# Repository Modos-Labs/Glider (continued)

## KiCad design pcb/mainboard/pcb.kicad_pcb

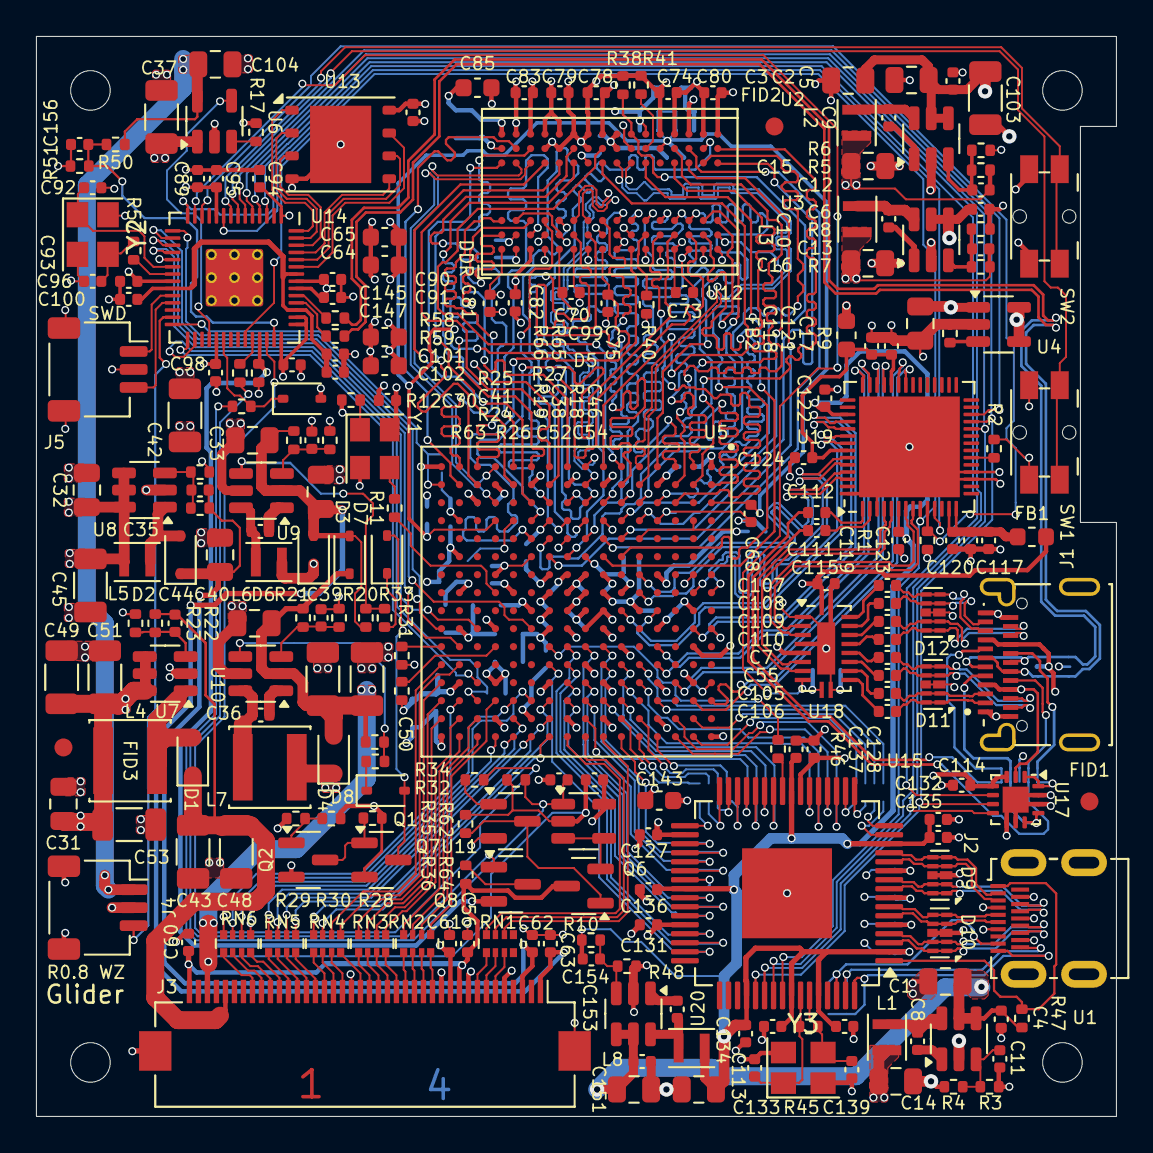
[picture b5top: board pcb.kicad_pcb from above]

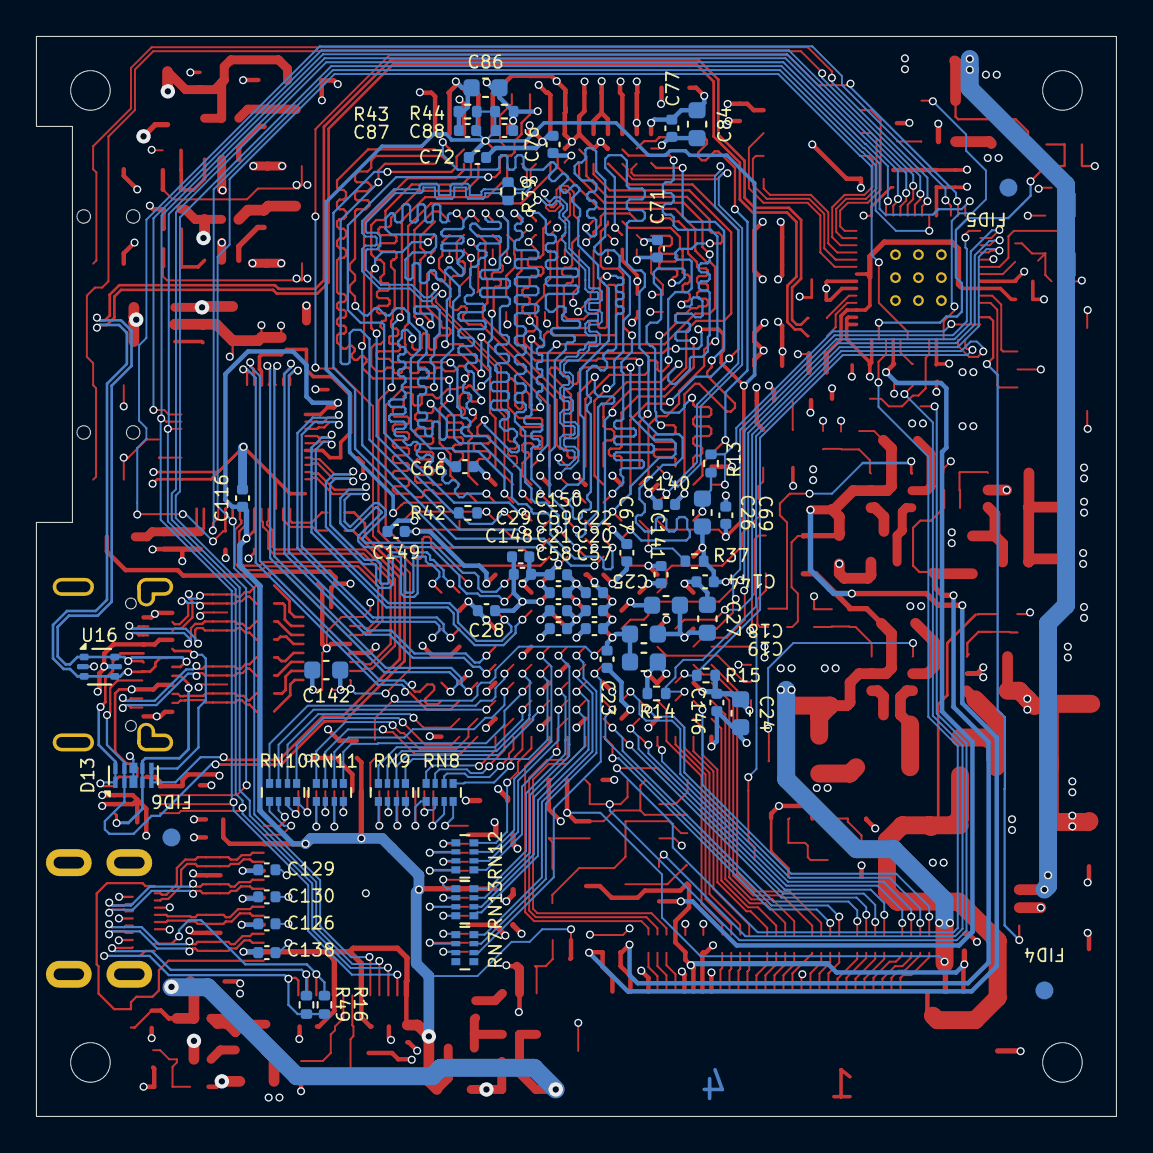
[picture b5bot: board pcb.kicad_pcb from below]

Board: 4 copper layers, 60.0 x 60.0 mm, 296 parts (61 on the bottom side), 307 nets.

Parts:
C1, C2, C3, C14, C15, C16, C17, C31, C32, C104, C151, C155: 10uF/10V; C_0805_2012Metric
C4, C5, C6, C7, C8, C9, C10, C35, C36, C54, C55, C87, C88, C90, C91, C94, C95, C96, C97, C98, C99, C100, C101, C105, C106, C107, C108, C109, C110, C111, C112, C114, C115, C119, C120, C121, C122, C123, C124, C127, C128, C129, C130, C131, C133, C134, C135, C136, C137, C138, C139, C152, C153, C156: 100nF; C_0402_1005Metric
C11, C12, C13, C154: 47pF; C_0402_1005Metric
C18, C19, C24, C25, C26, C27, C64, C65, C84, C85, C86, C142, C143, C145, C147: 47uF/6.3V; C_0603_1608Metric
C20, C22, C23, C28, C57, C59, C66, C144, C148: 4.7uF; C_0402_1005Metric
C21, C29, C58, C67, C140, C141, C146, C149, C150: 470nF; C_0402_1005Metric
C30, C52, C60, C61, C62, C63, C68, C69, C70, C71, C72, C73, C74, C75, C76, C77, C78, C79, C80, C81, C82, C83: 220nF; C_0402_1005Metric
C33, C34, C44, C46: 4.7uF/50V; C_0805_2012Metric
C37, C42, C45, C49, C51, C53, C103: 47uF/10V; C_1206_3216Metric
C38, C39, C40, C41, C92, C93, C113, C125: 18pF; C_0402_1005Metric
C43, C47, C48, C50: 10uF/50V; C_1206_3216Metric
C56, C89, C102, C116, C117, C118, C126, C132: 1uF; C_0402_1005Metric
D1, D2, D3, D4, D5, D6, D7, D8: B0530WS; D_SOD-323
D9, D10, D11, D12, D13: RCLAMP0524P; Diodes_UDFN-10_1.0x2.5mm_P0.5mm
FB1, FB2: 120R; L_0603_1608Metric
FID1, FID2, FID3, FID4, FID5, FID6: Fiducial; Fiducial_1mm_Mask2mm
H1, H2, H3, H4: MountingHole; MountingHole_2.2mm_M2_DIN965
J1: XUNPU TYPEC-324G-ACP24; XUNPU_TypeC-324G-ACP24
J2: XUNPU HDMI-101S; HDMI_Micro-D_Molex_46765-1x01_MOD
J3: FH12-40S-0.5SH; Hirose_FH12-40S-0.5SH_1x40-1MP_P0.50mm_Horizontal_Reversed
J4, J5: SM03B-SRSS-TB; JST_SH_SM03B-SRSS-TB_1x03-1MP_P1.00mm_Horizontal
L1, L2, L3, L5, L6, L8: FTC201610S4R7MBCA; L_Murata_DFE201610P
L4, L7: WPN4020H4R7MT; L_Changjiang_FNR4020S
Q1, Q7, Q8: AO3401A; SOT-23
Q2: S8050; SOT-23
Q6: AO3400A; SOT-23
R1, R2, R12, R13, R14, R21, R29, R38, R40, R42: 5.1K; R_0402_1005Metric
R3, R20, R26: 91K/1%; R_0402_1005Metric
R4, R5, R7, R8, R10, R64: 20K/1%; R_0402_1005Metric
R6: 16K/1%; R_0402_1005Metric
R9, R17, R19, R23, R25, R48, R65: 10K/1%; R_0402_1005Metric
R11, R46, R58, R59: 27R; R_0402_1005Metric
R15, R43, R44: 1K/1%; R_0402_1005Metric
R16, R47, R49: 10K; R_0402_1005Metric
R18, R22: 240K/1%; R_0402_1005Metric
R24: 360K/1%; R_0402_1005Metric
R27, R30: 27K/1%; R_0402_1005Metric
R28, R31, R32, R33, R34, R62: 120K/1%; R_0402_1005Metric
R35, R36: 0R; R_0402_1005Metric
R37, R39: 100R/1%; R_0402_1005Metric
R41: 240R/1%; R_0402_1005Metric
R45, R50, R51: 1M; R_0402_1005Metric
R57: 1K; R_0402_1005Metric
R63, R66: 51R; R_0402_1005Metric
RN1, RN2, RN3, RN4, RN5, RN6, RN7, RN8, RN9, RN10, RN11, RN12, RN13: 33R / 4D02WGF330JTCE; R_Array_Convex_4x0402
SW1, SW2: SW; Panasonic_EVQPUL_EVQPUC
U1, U2, U3, U20: SY8120; TSOT-23-6
U4, U6: MT9700; SOT-23-5
U5: XC6SLX16-FTG256; Xilinx_FTG256
U7, U8: MT3608(SOT23-6); SOT-23-6
U9, U10: LGS5148; TSOT-23-6
U11: LM321; SOT-23-5
U12: MT41K64M16TW; BGA-96_9.0x14.0mm_P0.8mm
U13: W25Q32JV; WSON-8-1EP_6x5mm_P1.27mm_EP3.4x4.3mm
U14: RP2040; RP2040-QFN-56
U15: ADV7611; LQFP-64-1EP_10x10mm_P0.5mm_EP5x5mm
U16: USBLC6-2P6; SOT-666
U17: FUSB302BMPX; WQFN-14-1EP_2.5x2.5mm_P0.5mm_EP1.45x1.45mm
U18: CBTL02043A; WQFN-20-1EP_2.5x4.5mm_P0.5mm_EP1x2.9mm
U19: PTN3460; QFN-56-1EP_7x7mm_P0.4mm_EP5.6x5.6mm
Y1: 33MHz; Oscillator_SMD_Abracon_ASE-4Pin_3.2x2.5mm
Y2: 12MHz; Crystal_SMD_3225-4Pin_3.2x2.5mm
Y3: 28.63636MHz; Crystal_SMD_3225-4Pin_3.2x2.5mm

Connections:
+1V2: C13.2, C16.2, C18.1, C19.1, C20.1, C21.1, C22.1, C23.1, C59.1, L3.2, R7.2, U5.G7 (VCCINT), U5.G9 (VCCINT), U5.H8 (VCCINT), U5.H10 (VCCINT), U5.J7 (VCCINT), U5.J9 (VCCINT), U5.K8 (VCCINT), U5.K10 (VCCINT)
+1V8: C116.1, C119.1, C122.1, C132.1, C133.1, C134.1, C135.1, C136.1, C137.1, C138.1, C139.1, C154.2, C155.2, L8.2, R10.2, U15.2 (CVDD), U15.14 (CVDD), U15.24 (DVDD), U15.40 (DVDD), U15.52 (DVDD), U15.57 (PVDD), U15.60 (DVDD), U19.6 (VDD18), U19.45 (VDD18)
+1V35: C12.2, C15.2, C64.1, C65.1, C66.1, C67.1, C70.1, C71.1, C73.1, C74.1, C76.1, C77.1, C78.1, C79.1, C80.1, C81.1, C82.1, C83.1, C84.1, C85.1, C86.1, C87.1, C140.1, L2.2, R5.2, R43.1, U5.D2 (VCCO_3), U5.G4 (VCCO_3), U5.J2 (VCCO_3), U5.K4 (VCCO_3), U5.N2 (VCCO_3), U12.A1 (VDDQ), U12.A8 (VDDQ), U12.B2 (VDD), U12.C1 (VDDQ), U12.C9 (VDDQ), U12.D2 (VDDQ), U12.D9 (VDD), U12.E9 (VDDQ), U12.F1 (VDDQ), U12.G7 (VDD), U12.H2 (VDDQ), U12.H9 (VDDQ), U12.K2 (VDD), U12.K8 (VDD), U12.N1 (VDD), U12.N9 (VDD), U12.R1 (VDD), U12.R9 (VDD)
+3V3: C11.2, C14.2, C24.1, C25.1, C26.1, C27.1, C28.1, C29.1, C30.2, C57.1, C58.1, C61.1, C89.1, C90.1, C91.1, C94.1, C95.1, C96.1, C97.1, C98.1, C99.1, C114.1, C115.1, C126.1, C127.1, C128.1, C129.1, C130.1, C131.1, C141.1, C142.1, C143.1, C144.1, C145.1, C146.1, C147.1, C148.1, C149.1, C150.1, FB1.1, FB2.1, J3.5, J3.11, L1.2, Q7.2 (S), R3.2, R12.1, R13.1, R15.1, R35.1, R36.1, R65.1, U5.B4 (VCCO_0), U5.B9 (VCCO_0), U5.B13 (VCCO_0), U5.D7 (VCCO_0), U5.D10 (VCCO_0), U5.D15 (VCCO_1), U5.E5 (VCCAUX), U5.F8 (VCCAUX), U5.F11 (VCCAUX), U5.G10 (VCCAUX), U5.G13 (VCCO_1), U5.H6 (VCCAUX), U5.J10 (VCCAUX), U5.J15 (VCCO_1), U5.K13 (VCCO_1), U5.L6 (VCCAUX), U5.L9 (VCCAUX), U5.N7 (VCCO_2), U5.N10 (VCCO_2), U5.N15 (VCCO_1), U5.R4 (VCCO_2), U5.R8 (VCCO_2), U5.R13 (VCCO_1), U13.8 (VCC), U14.1 (IOVDD), U14.10 (IOVDD), U14.22 (IOVDD), U14.33 (IOVDD), U14.42 (IOVDD), U14.43 (ADC_AVDD), U14.44 (VREG_IN), U14.48 (USB_VDD), U14.49 (IOVDD), U15.5 (TVDD), U15.8 (TVDD), U15.11 (TVDD), U15.23 (DVDDIO), U15.34 (DVDDIO), U15.44 (DVDDIO), U17.3 (VDD), U17.4 (VDD), U18.1 (VDD), U18.6 (VDD), U18.10 (VDD), Y1.4 (Vdd)
+5V: C1.2, C2.2, C3.2, C4.2, C5.2, C6.2, C17.2, C103.2, C151.2, C152.2, R47.1, U1.4 (~SHDN), U1.5 (IN), U2.4 (~SHDN), U2.5 (IN), U3.4 (~SHDN), U3.5 (IN), U4.1 (VOUT), U20.4 (~SHDN), U20.5 (IN)
+5V_EPD: C31.2, C32.2, C33.2, C34.2, C37.2, C42.2, C45.2, C49.2, C51.2, C53.2, L4.1, L5.1, Q1.2 (S), R28.2, R30.1, U6.1 (VOUT), U7.4 (~SHDN), U7.5 (VIN), U7.6 (NC), U8.4 (~SHDN), U8.5 (VIN), U8.6 (NC), U9.5 (IN), U10.5 (IN)
+DRAM_VREF: C68.1, C69.1, C72.1, C75.1, C87.2, C88.1, R43.2, R44.1, U5.A3 (IO_L83N_VREF_3), U5.N4 (IO_L2N_3), U12.H1 (VrefDQ), U12.M8 (VrefCA)
/dp_in/CC1: D13.4 (IO3), D13.7 (NC2), J1.A5 (CC1), U17.10 (CC1), U17.11 (CC1)
/dp_in/CC2: D13.1 (IO1), D13.10 (NC4), J1.B5 (CC2), U17.1 (CC2), U17.14 (CC2)
/dp_in/DP0N: U18.7 (A1_P), U19.5 (DP0_N)
/dp_in/DP0P: U18.8 (A1_N), U19.4 (DP0_P)
/dp_in/DP1N: U18.3 (A0_P), U19.8 (DP1_N)
/dp_in/DP1P: U18.4 (A0_N), U19.7 (DP1_P)
/dp_in/DPAUXN: C112.2, U19.1 (AUX_N)
/dp_in/DPAUXP: C111.2, U19.2 (AUX_P)
/dp_in/RX1N: C105.1, D11.2 (IO2), D11.9 (NC3), J1.A3 (TX1-)
/dp_in/RX1NC: C105.2, U18.13 (C1_P)
/dp_in/RX1P: C106.1, D11.1 (IO1), D11.10 (NC4), J1.A2 (TX1+)
/dp_in/RX1PC: C106.2, U18.12 (C1_N)
/dp_in/RX2N: C109.1, D12.2 (IO2), D12.9 (NC3), J1.B3 (TX2-)
/dp_in/RX2NC: C109.2, U18.17 (B1_P)
/dp_in/RX2P: C110.1, D12.1 (IO1), D12.10 (NC4), J1.B2 (TX2+)
/dp_in/RX2PC: C110.2, U18.16 (B1_N)
/dp_in/SBU1: C111.1, D13.5 (IO4), D13.6 (NC1), J1.A8 (SBU1)
/dp_in/SBU2: C112.1, D13.2 (IO2), D13.9 (NC3), J1.B8 (SBU2)
/dp_in/TX1N: C7.1, D11.5 (IO4), D11.6 (NC1), J1.B10 (RX1-)
/dp_in/TX1NC: C7.2, U18.15 (C0_P)
/dp_in/TX1P: C55.1, D11.4 (IO3), D11.7 (NC2), J1.B11 (RX1+)
/dp_in/TX1PC: C55.2, U18.14 (C0_N)
/dp_in/TX2N: C107.1, D12.5 (IO4), D12.6 (NC1), J1.A10 (RX2-)
/dp_in/TX2NC: C107.2, U18.19 (B0_P)
/dp_in/TX2P: C108.1, D12.4 (IO3), D12.7 (NC2), J1.A11 (RX2+)
/dp_in/TX2PC: C108.2, U18.18 (B0_N)
/eink/ED0: J3.14, RN2.3 (R3.1)
/eink/ED1: J3.15, RN2.2 (R2.1)
/eink/ED2: J3.16, RN2.1 (R1.1)
/eink/ED3: J3.17, RN3.4 (R4.1)
/eink/ED4: J3.18, RN3.3 (R3.1)
/eink/ED5: J3.19, RN3.2 (R2.1)
/eink/ED6: J3.20, RN3.1 (R1.1)
/eink/ED7: J3.21, RN4.4 (R4.1)
/eink/ED8: J3.23, RN4.3 (R3.1)
/eink/ED9: J3.24, RN4.2 (R2.1)
/eink/ED10: J3.25, RN4.1 (R1.1)
/eink/ED11: J3.26, RN5.4 (R4.1)
/eink/ED12: J3.27, RN5.3 (R3.1)
/eink/ED13: J3.28, RN5.2 (R2.1)
/eink/ED14: J3.29, RN5.1 (R1.1)
/eink/ED15: J3.30, RN6.4 (R4.1)
/eink/EN_VGL: R31.1, R33.2, U9.4 (~SHDN)
/eink/EN_VNEG: R32.1, R34.2, U10.4 (~SHDN)
/eink/ESDCLK: J3.13, RN2.4 (R4.1)
/eink/ESDLE: J3.32, RN6.2 (R2.1)
/eink/ESDOE: J3.33, RN6.1 (R1.1)
/eink/GDCLK: J3.7, RN1.2 (R2.1)
/eink/GDOE: J3.6, RN1.3 (R3.1)
/eink/GDSP: J3.8, RN1.1 (R1.1)
/eink/SDCE0: J3.31, RN6.3 (R3.1)
/fpga_ddr/DRAM_ADDR0: U5.K5 (IO_L47P_M3A0_3), U12.N3 (A0)
/fpga_ddr/DRAM_ADDR1: U5.K6 (IO_L47N_M3A1_3), U12.P7 (A1)
/fpga_ddr/DRAM_ADDR2: U5.D1 (IO_L49N_M3A2_3), U12.P3 (A2)
/fpga_ddr/DRAM_ADDR3: U5.L4 (IO_L45P_M3A3_3), U12.N2 (A3)
/fpga_ddr/DRAM_ADDR4: U5.G5 (IO_L51N_M3A4_3), U12.P8 (A4)
/fpga_ddr/DRAM_ADDR5: U5.H4 (IO_L44P_GCLK21_M3A5_3), U12.P2 (A5)
/fpga_ddr/DRAM_ADDR6: U5.H3 (IO_L44N_GCLK20_M3A6_3), U12.R8 (A6)
/fpga_ddr/DRAM_ADDR7: U5.D3 (IO_L49P_M3A7_3), U12.R2 (A7)
/fpga_ddr/DRAM_ADDR8: U5.B2 (IO_L52P_M3A8_3), U12.T8 (A8)
/fpga_ddr/DRAM_ADDR9: U5.A2 (IO_L52N_M3A9_3), U12.R3 (A9)
/fpga_ddr/DRAM_ADDR10: U5.G6 (IO_L51P_M3A10_3), U12.L7 (A10)
/fpga_ddr/DRAM_ADDR11: U5.E3 (IO_L54N_M3A11_3), U12.R7 (A11)
/fpga_ddr/DRAM_ADDR12: U5.F3 (IO_L53N_M3A12_3), U12.N7 (A12/~BC)
/fpga_ddr/DRAM_ADDR13: U5.F6 (IO_L55P_M3A13_3), U12.T3 (A13)
/fpga_ddr/DRAM_ADDR14: U5.F5 (IO_L55N_M3A14_3), U12.T7 (A14/NC)
/fpga_ddr/DRAM_BA0: U5.C3 (IO_L48P_M3BA0_3), U12.M2 (BA0)
/fpga_ddr/DRAM_BA1: U5.C2 (IO_L48N_M3BA1_3), U12.N8 (BA1)
/fpga_ddr/DRAM_BA2: U5.B1 (IO_L50N_M3BA2_3), U12.M3 (BA2)
/fpga_ddr/DRAM_CASB: U5.H5 (IO_L43N_GCLK22_IRDY2_M3CASN_3), U12.K3 (~CAS)
/fpga_ddr/DRAM_CKE: R38.1, U5.F4 (IO_L53P_M3CKE_3), U12.K9 (CKE)
/fpga_ddr/DRAM_CKN: R39.1, U5.E1 (IO_L46N_M3CLKN_3), U12.K7 (~CK)
/fpga_ddr/DRAM_CKP: R39.2, U5.E2 (IO_L46P_M3CLK_3), U12.J7 (CK)
/fpga_ddr/DRAM_CSB: R40.1, U12.L2 (~CS)
/fpga_ddr/DRAM_DATA0: U5.K2 (IO_L37P_M3DQ0_3), U12.E3 (DQ0)
/fpga_ddr/DRAM_DATA1: U5.K1 (IO_L37N_M3DQ1_3), U12.F7 (DQ1)
/fpga_ddr/DRAM_DATA2: U5.J3 (IO_L38P_M3DQ2_3), U12.F2 (DQ2)
/fpga_ddr/DRAM_DATA3: U5.J1 (IO_L38N_M3DQ3_3), U12.F8 (DQ3)
/fpga_ddr/DRAM_DATA4: U5.F2 (IO_L41P_GCLK27_M3DQ4_3), U12.H3 (DQ4)
/fpga_ddr/DRAM_DATA5: U5.F1 (IO_L41N_GCLK26_M3DQ5_3), U12.H8 (DQ5)
/fpga_ddr/DRAM_DATA6: U5.G3 (IO_L40P_M3DQ6_3), U12.G2 (DQ6)
/fpga_ddr/DRAM_DATA7: U5.G1 (IO_L40N_M3DQ7_3), U12.H7 (DQ7)
/fpga_ddr/DRAM_DATA8: U5.L3 (IO_L36P_M3DQ8_3), U12.D7 (DQ8)
/fpga_ddr/DRAM_DATA9: U5.L1 (IO_L36N_M3DQ9_3), U12.C3 (DQ9)
/fpga_ddr/DRAM_DATA10: U5.M2 (IO_L35P_M3DQ10_3), U12.C8 (DQ10)
/fpga_ddr/DRAM_DATA11: U5.M1 (IO_L35N_M3DQ11_3), U12.C2 (DQ11)
/fpga_ddr/DRAM_DATA12: U5.P2 (IO_L33P_M3DQ12_3), U12.A7 (DQ12)
/fpga_ddr/DRAM_DATA13: U5.P1 (IO_L33N_M3DQ13_3), U12.A2 (DQ13)
/fpga_ddr/DRAM_DATA14: U5.R2 (IO_L32P_M3DQ14_3), U12.B8 (DQ14)
/fpga_ddr/DRAM_DATA15: U5.R1 (IO_L32N_M3DQ15_3), U12.A3 (DQ15)
/fpga_ddr/DRAM_LDM: U5.J4 (IO_L42N_GCLK24_M3LDM_3), U12.E7 (LDM)
/fpga_ddr/DRAM_LDQSN: U5.H1 (IO_L39N_M3LDQSN_3), U12.G3 (~LDQS)
/fpga_ddr/DRAM_LDQSP: U5.H2 (IO_L39P_M3LDQS_3), U12.F3 (LDQS)
/fpga_ddr/DRAM_ODT: U5.L5 (IO_L45N_M3ODT_3), U12.K1 (ODT)
/fpga_ddr/DRAM_RASB: U5.J6 (IO_L43P_GCLK23_M3RASN_3), U12.J3 (~RAS)
/fpga_ddr/DRAM_RST: R42.1, U5.E4 (IO_L54P_M3RESET_3), U12.T2 (~RESET)
/fpga_ddr/DRAM_UDM: U5.K3 (IO_L42P_GCLK25_TRDY2_M3UDM_3), U12.D3 (UDM)
/fpga_ddr/DRAM_UDQSN: U5.N1 (IO_L34N_M3UDQSN_3), U12.B7 (~UDQS)
/fpga_ddr/DRAM_UDQSP: U5.N3 (IO_L34P_M3UDQS_3), U12.C7 (UDQS)
/fpga_ddr/DRAM_WEB: U5.C1 (IO_L50P_M3WE_3), U12.L3 (~WE)
/mcu/MCU_1V1: C100.1, C101.1, C102.1, U14.23 (DVDD), U14.45 (VREG_VOUT), U14.50 (DVDD)
/mcu/QSPI_SCLK: U13.6 (CLK), U14.52 (QSPI_SCLK)
/mcu/QSPI_SD0: U13.5 (DI(IO0)), U14.53 (QSPI_SD0)
/mcu/QSPI_SD1: U13.2 (DO(IO1)), U14.55 (QSPI_SD1)
/mcu/QSPI_SD2: U13.3 (IO2), U14.54 (QSPI_SD2)
/mcu/QSPI_SD3: U13.7 (IO3), U14.51 (QSPI_SD3)
/mcu/QSPI_SS: U13.1 (~CS), U14.56 (QSPI_SS)
/mcu/SWCLK: J5.1, U14.24 (SWCLK)
/mcu/SWD: J5.3, U14.25 (SWD)
/mcu/XIN: C92.1, U14.20 (XIN), Y2.1
/mcu/XOUT: R57.1, U14.21 (XOUT)
/tmds_in/ADV_CK: R46.2, U15.25 (LLC)
/tmds_in/ADV_DE: RN7.1 (R1.1), U15.45 (DE)
/tmds_in/ADV_HS: RN7.2 (R2.1), U15.46 (HS)
/tmds_in/ADV_P0: RN13.4 (R4.1), U15.43 (P0)
/tmds_in/ADV_P1: RN13.3 (R3.1), U15.42 (P1)
/tmds_in/ADV_P2: RN13.2 (R2.1), U15.41 (P2)
/tmds_in/ADV_P3: RN13.1 (R1.1), U15.39 (P3)
/tmds_in/ADV_P4: RN12.4 (R4.1), U15.38 (P4)
/tmds_in/ADV_P5: RN12.3 (R3.1), U15.37 (P5)
/tmds_in/ADV_P6: RN12.2 (R2.1), U15.36 (P6)
/tmds_in/ADV_P7: RN12.1 (R1.1), U15.35 (P7)
/tmds_in/ADV_P8: RN8.4 (R4.1), U15.33 (P8)
/tmds_in/ADV_P9: RN8.3 (R3.1), U15.32 (P9)
/tmds_in/ADV_P10: RN8.2 (R2.1), U15.31 (P10)
/tmds_in/ADV_P11: RN8.1 (R1.1), U15.30 (P11)
/tmds_in/ADV_P12: RN9.4 (R4.1), U15.29 (P12)
/tmds_in/ADV_P13: RN9.3 (R3.1), U15.28 (P13)
/tmds_in/ADV_P14: RN9.2 (R2.1), U15.27 (P14)
/tmds_in/ADV_P15: RN9.1 (R1.1), U15.26 (P15)
/tmds_in/ADV_P16: RN11.4 (R4.1), U15.22 (P16)
/tmds_in/ADV_P17: RN11.3 (R3.1), U15.21 (P17)
/tmds_in/ADV_P18: RN11.2 (R2.1), U15.20 (P18)
/tmds_in/ADV_P19: RN11.1 (R1.1), U15.19
/tmds_in/ADV_P20: RN10.4 (R4.1), U15.18 (P20)
/tmds_in/ADV_P21: RN10.3 (R3.1), U15.17 (P21)
/tmds_in/ADV_P22: RN10.2 (R2.1), U15.16 (P22)
/tmds_in/ADV_P23: RN10.1 (R1.1), U15.15 (P23)
/tmds_in/ADV_VS: RN7.3 (R3.1), U15.47 (VS/FIELD/ALSB)
/tmds_in/HDMI_5V: J2.19 (+5V), R16.2, R49.2, U15.64 (RXA_5V)
/tmds_in/HDMI_HPD: J2.1 (HPD/HEAC-), R47.2, U15.1 (HPA_A/INT2)
/tmds_in/HDMI_SCL: J2.17 (SCL), R16.1, U15.62 (DDCA_SCL)
/tmds_in/HDMI_SDA: J2.18 (SDA), R49.1, U15.63 (DDCA_SDA)
/tmds_in/TMDS_CKN: D10.1 (IO1), D10.10 (NC4), J2.14 (CK-), U15.3 (RXA_C-)
/tmds_in/TMDS_CKP: D10.2 (IO2), D10.9 (NC3), J2.12 (CK+), U15.4 (RXA_C+)
/tmds_in/TMDS_D0N: D10.4 (IO3), D10.7 (NC2), J2.11 (D0-), U15.6 (RXA_0-)
/tmds_in/TMDS_D0P: D10.5 (IO4), D10.6 (NC1), J2.9 (D0+), U15.7 (RXA_0+)
/tmds_in/TMDS_D1N: D9.1 (IO1), D9.10 (NC4), J2.8 (D1-), U15.9 (RXA_1-)
/tmds_in/TMDS_D1P: D9.2 (IO2), D9.9 (NC3), J2.6 (D1+), U15.10 (RXA_1+)
/tmds_in/TMDS_D2N: D9.4 (IO3), D9.7 (NC2), J2.5 (D2-), U15.12 (RXA_2-)
/tmds_in/TMDS_D2P: D9.5 (IO4), D9.6 (NC1), J2.3 (D2+), U15.13 (RXA_2+)
ADV_INT: U14.3 (GPIO1), U15.55 (INT1)
DEC_RST: U14.37 (GPIO25), U15.56 (~RESET), U19.9 (RST_N)
DPI_B0: RN13.5 (R4.2), U5.J13 (IO_L41P_GCLK9_IRDY1_M1RASN_1)
DPI_B1: RN13.6 (R3.2), U5.J14 (IO_L43P_GCLK5_M1DQ4_1)
DPI_B2: RN13.7 (R2.2), U5.H11 (IO_L38N_A4_M1CLKN_1)
DPI_B3: RN13.8 (R1.2), U5.H13 (IO_L39P_M1A3_1)
DPI_B4: RN12.5 (R4.2), U5.H15 (IO_L37P_A7_M1A0_1)
DPI_B5: RN12.6 (R3.2), U5.H14 (IO_L39N_M1ODT_1)
DPI_B6: RN12.7 (R2.2), U5.G11 (IO_L30N_A20_M1A11_1)
DPI_B7: RN12.8 (R1.2), U5.F16 (IO_L35N_A10_M1A2_1)
DPI_DE: RN7.8 (R1.2), U5.J12 (IO_L40N_GCLK10_M1A6_1)
DPI_G0: RN8.5 (R4.2), U5.F15 (IO_L35P_A11_M1A7_1)
DPI_G1: RN8.6 (R3.2), U5.E16 (IO_L34N_A12_M1BA2_1)
DPI_G2: RN8.7 (R2.2), U5.E15 (IO_L34P_A13_M1WE_1)
DPI_G3: RN8.8 (R1.2), U5.D16 (IO_L31N_A18_M1A12_1)
DPI_G4: RN9.5 (R4.2), U5.G12 (IO_L38P_A5_M1CLK_1)
DPI_G5: RN9.6 (R3.2), U5.G14 (IO_L36P_A9_M1BA0_1)
DPI_G6: RN9.7 (R2.2), U5.F12 (IO_L30P_A21_M1RESET_1)
DPI_G7: RN9.8 (R1.2), U5.F14 (IO_L32N_A16_M1A9_1)
DPI_HS: RN7.7 (R2.2), U5.J11 (IO_L40P_GCLK11_M1A5_1)
DPI_PCLK: R46.1, U5.K11 (IO_L42N_GCLK6_TRDY1_M1LDM_1)
DPI_R0: RN11.5 (R4.2), U5.F13 (IO_L32P_A17_M1A8_1)
DPI_R1: RN11.6 (R3.2), U5.E13 (IO_L1P_A25_1)
DPI_R2: RN11.7 (R2.2), U5.C16 (IO_L33N_A14_M1A4_1)
DPI_R3: RN11.8 (R1.2), U5.C15 (IO_L33P_A15_M1A10_1)
DPI_R4: RN10.5 (R4.2), U5.B16 (IO_L29N_A22_M1A14_1)
DPI_R5: RN10.6 (R3.2), U5.B15 (IO_L29P_A23_M1A13_1)
DPI_R6: RN10.7 (R2.2), U5.D14 (IO_L31P_A19_M1CKE_1)
DPI_R7: RN10.8 (R1.2), U5.E12 (IO_L1N_A24_VREF_1)
DPI_VS: RN7.6 (R3.2), U5.K12 (IO_L42P_GCLK7_M1UDM_1)
DP_HPD: U14.9 (GPIO7), U19.11 (HPDRX)
DP_PDN: R1.2, U14.12 (GPIO9), U19.10 (PD_N)
DP_VALID: U14.6 (GPIO4), U19.26 (BKLTEN)
EPDC_D0: RN2.6 (R3.2), U5.P16 (IO_L48N_M1DQ9_1)
EPDC_D1: RN2.7 (R2.2), U5.P15 (IO_L48P_HDC_M1DQ8_1)
EPDC_D2: RN2.8 (R1.2), U5.R16 (IO_L49N_M1DQ11_1)
EPDC_D3: RN3.5 (R4.2), U5.R15 (IO_L49P_M1DQ10_1)
EPDC_D4: RN3.6 (R3.2), U5.T15 (IO_L50N_M1UDQSN_1)
EPDC_D5: RN3.7 (R2.2), U5.T14 (IO_L51P_M1DQ12_1)
EPDC_D6: RN3.8 (R1.2), U5.T13 (IO_L51N_M1DQ13_1)
EPDC_D7: RN4.5 (R4.2), U5.R12 (IO_L52P_M1DQ14_1)
EPDC_D8: RN4.6 (R3.2), U5.T12 (IO_L52N_M1DQ15_1)
EPDC_D9: RN4.7 (R2.2), U5.K16 (IO_L44N_A2_M1DQ7_1)
EPDC_D10: RN4.8 (R1.2), U5.K14 (IO_L41N_GCLK8_M1CASN_1)
EPDC_D11: RN5.5 (R4.2), U5.K15 (IO_L44P_A3_M1DQ6_1)
EPDC_D12: RN5.6 (R3.2), U5.L16 (IO_L47N_LDC_M1DQ1_1)
EPDC_D13: RN5.7 (R2.2), U5.M15 (IO_L46P_FCS_B_M1DQ2_1)
EPDC_D14: RN5.8 (R1.2), U5.M16 (IO_L46N_FOE_B_M1DQ3_1)
EPDC_D15: RN6.5 (R4.2), U5.N16 (IO_L45N_A0_M1LDQSN_1)
EPDC_GDCLK: RN1.7 (R2.2), U5.H16 (IO_L37N_A6_M1A1_1)
EPDC_GDOE: RN1.6 (R3.2), U5.G16 (IO_L36N_A8_M1BA1_1)
EPDC_GDSP: RN1.8 (R1.2), U5.J16 (IO_L43N_GCLK4_M1DQ5_1)
EPDC_SDCE0: RN6.6 (R3.2), U5.L14 (IO_L47P_FWE_B_M1DQ0_1)
EPDC_SDCLK: RN2.5 (R4.2), U5.N14 (IO_L45P_A1_M1LDQS_1)
EPDC_SDLE: RN6.7 (R2.2), U5.M14 (IO_L74N_DOUT_BUSY_1)
EPDC_SDOE: RN6.8 (R1.2), U5.R14 (IO_L50P_M1UDQS_1)
EPD_PWR_EN: U6.4 (EN), U14.32 (GPIO21)
EPD_VCOM_PWM: D5.1 (K), R27.2, U14.34 (GPIO22)
FL_PWM: J4.3, U14.27 (GPIO16)
FPGA_CS: U5.L10 (IO_L16P_2), U14.16 (GPIO13)
FPGA_DONE: R15.2, U5.P13 (DONE_2), U14.29 (GPIO18)
FPGA_MISO: U5.T10 (IO_L3N_MOSI_CSI_B_MISO0_2), U14.15 (GPIO12)
FPGA_MOSI: U5.P10 (IO_L3P_D0_DIN_MISO_MISO1_2), U14.18 (GPIO15)
FPGA_PROG: R13.2, U5.T2 (PROGRAM_B_2), U14.28 (GPIO17)
FPGA_SCLK: U5.R11 (IO_L1P_CCLK_2), U14.17 (GPIO14)
FPGA_SUSP: R14.1, U5.P14 (SUSPEND), U14.30 (GPIO19)
GCLK: R11.1, U5.N8 (IO_L29N_GCLK2_2)
GND: C1.1, C2.1, C3.1, C4.1, C5.1, C6.1, C14.1, C15.1, C16.1, C17.1, C18.2, C19.2, C20.2, C21.2, C22.2, C23.2, C24.2, C25.2, C26.2, C27.2, C28.2, C29.2, C30.1, C31.1, C32.1, C37.1, C38.2, C39.2, C42.1, C43.1, C44.1, C45.1, C46.2, C47.2, C48.1, C49.1, C50.2, C51.1, C52.1, C53.1, C54.1, C56.1, C57.2, C58.2, C59.2, C60.2, C61.2, C62.2, C63.2, C64.2, C65.2, C66.2, C67.2, C68.2, C69.2, C70.2, C71.2, C72.2, C73.2, C74.2, C75.2, C76.2, C77.2, C78.2, C79.2, C80.2, C81.2, C82.2, C83.2, C84.2, C85.2, C86.2, C88.2, C89.2, C90.2, C91.2, C92.2, C93.2, C94.2, C95.2, C96.2, C97.2, C98.2, C99.2, C100.2, C101.2, C102.2, C103.1, C104.1, C113.2, C114.2, C115.2, C116.2, C117.2, C118.2, C119.2, C120.2, C121.2, C122.2, C123.2, C124.2, C125.2, C126.2, C127.2, C128.2, C129.2, C130.2, C131.2, C132.2, C133.2, C134.2, C135.2, C136.2, C137.2, C138.2, C139.2, C140.2, C141.2, C142.2, C143.2, C144.2, C145.2, C146.2, C147.2, C148.2, C149.2, C150.2, C151.1, C152.1, C155.1, C156.2, D3.1 (K), D4.1 (K), D5.2 (A), D9.3 (GND), D9.8 (GND), D10.3 (GND), D10.8 (GND), D11.3 (GND), D11.8 (GND), D12.3 (GND), D12.8 (GND), D13.3 (GND), D13.8 (GND), J1.A1 (GND)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
I2C_SCL: U14.5 (GPIO3), U15.53 (SCL), U17.6 (SCL), U19.25 (MS_SCL)
I2C_SDA: U14.4 (GPIO2), U15.54 (SDA), U17.7 (SDA), U19.24 (MS_SDA)
KEY: SW2.1, U14.8 (GPIO6)
KEY2: SW1.1, U14.7 (GPIO5)
LVDS_EVEN_AN: U5.D11 (IO_L66P_SCP1_0), U19.42 (LVSAE_N)
LVDS_EVEN_AP: U5.D12 (IO_L66N_SCP0_0), U19.41 (LVSAE_P)
LVDS_EVEN_BN: U5.C13 (IO_L63P_SCP7_0), U19.40 (LVSBE_N)
LVDS_EVEN_BP: U5.A13 (IO_L63N_SCP6_0), U19.39 (LVSBE_P)
LVDS_EVEN_CN: U5.A14 (IO_L65N_SCP2_0), U19.37 (LVSCE_N)
LVDS_EVEN_CP: U5.B14 (IO_L65P_SCP3_0), U19.36 (LVSCE_P)
LVDS_ODD_AN: U5.E7 (IO_L36P_GCLK15_0), U19.54 (LVSAO_N)
LVDS_ODD_AP: U5.E8 (IO_L36N_GCLK14_0), U19.53 (LVSAO_P)
LVDS_ODD_BN: U5.B8 (IO_L33P_0), U19.52 (LVSBO_N)
LVDS_ODD_BP: U5.A8 (IO_L33N_0), U19.51 (LVSBO_P)
LVDS_ODD_CKN: U5.B10 (IO_L35P_GCLK17_0), U19.47 (LVSCKO_N)
LVDS_ODD_CKP: U5.A10 (IO_L35N_GCLK16_0), U19.46 (LVSCKO_P)
LVDS_ODD_CN: U5.D9 (IO_L40N_0), U19.49 (LVSCO_N)
LVDS_ODD_CP: U5.F9 (IO_L40P_0), U19.48 (LVSCO_P)
unnamed: C93.1, R57.2, Y2.3
unnamed: C117.1, C120.1, C123.1, FB1.2, U19.13 (VDD33), U19.14 (VDD33)
unnamed: C118.1, C121.1, C124.1, FB2.2, U19.38 (VDD33), U19.50 (VDD33)
unnamed: D1.2 (A), L4.2, U7.1 (SW)
unnamed: D2.2 (A), L5.2, U8.1 (SW)
unnamed: D7.2 (A), D8.2 (A), Q1.3 (D)
unnamed: D7.1 (K), R31.2
unnamed: D8.1 (K), R32.2
unnamed: Q1.1 (G), Q2.3 (C), R28.1
unnamed: Q2.1 (B), R29.2, R30.2
unnamed: Q6.1 (G), Q7.3 (D), R62.1
unnamed: Q6.2 (S), U11.3 (-), U11.4
unnamed: Q7.1 (G), R63.2
unnamed: Q8.3 (D), R64.1
unnamed: Q8.1 (G), R66.1
unnamed: C8.2, U1.1 (BS)
unnamed: C11.1, R3.1, R4.2, U1.3 (FB)
unnamed: C8.1, L1.1, U1.6 (SW)
unnamed: C9.2, U2.1 (BS)
unnamed: C12.1, R5.1, R6.2, U2.3 (FB)
unnamed: C9.1, L2.1, U2.6 (SW)
unnamed: C10.2, U3.1 (BS)
unnamed: C13.1, R7.1, R8.2, U3.3 (FB)
unnamed: C10.1, L3.1, U3.6 (SW)
unnamed: R9.2, U4.3 (SET)
unnamed: R35.2, U5.T11 (IO_L1N_M0_CMPMISO_2)
unnamed: R37.1, U5.M4 (IO_L1P_3)
unnamed: R36.2, U5.N11 (IO_L13P_M1_2)
unnamed: R17.2, U6.3 (SET)
unnamed: C40.1, R22.1, R23.2, U7.3 (NFB)
unnamed: C41.1, R24.1, R25.2, U8.3 (NFB)
unnamed: C35.2, U9.1 (BS)
unnamed: C38.1, R18.1, R19.2, U9.3 (FB)
unnamed: C35.1, L6.1, U9.6 (SW)
unnamed: C36.2, U10.1 (BS)
unnamed: C39.1, R20.1, R21.2, U10.3 (FB)
unnamed: C36.1, L7.1, U10.6 (SW)
unnamed: C52.2, R26.2, R27.1, U11.1 (+)
unnamed: R41.1, U12.L8 (ZQ)
unnamed: R59.2, U14.46 (USB_DM)
unnamed: R58.2, U14.47 (USB_DP)
unnamed: C125.1, R45.1, U15.59 (XTALN), Y3.3
unnamed: C113.1, R45.2, U15.58 (XTALP), Y3.1
unnamed: R2.2, U19.20 (TESTMODE)
unnamed: C153.2, U20.1 (BS)
unnamed: C154.1, R10.1, R48.2, U20.3 (FB)
unnamed: C153.1, L8.1, U20.6 (SW)
unnamed: R12.2, Y1.1 (EN)
unnamed: R11.2, Y1.3 (OUT)
TCPC_INT: U14.14 (GPIO11), U17.5 (INT_N)
TYPEC_ORI: U14.13 (GPIO10), U18.9 (SEL)
USB_DN: J1.A7 (D-), J1.B7 (D-), R59.1, U16.3 (I/O2), U16.4 (I/O2)
USB_DP: J1.A6 (D+), J1.B6 (D+), R58.1, U16.1 (I/O1), U16.6 (I/O1)
VBUS: C104.2, J1.A4 (VBUS), J1.A9 (VBUS), J1.B4 (VBUS), J1.B9 (VBUS), J4.1, R50.1, U4.4 (EN), U4.5 (VIN), U6.5 (VIN), U16.5 (VBUS), U17.2 (VBUS)
VBUS_MEA: C156.1, R50.2, R51.1, U14.41 (GPIO29_ADC3)
VCOM: C56.2, C60.1, J3.10, J3.40, Q6.3 (D), R64.2
VCOM_EN: R63.1, U14.40 (GPIO28_ADC2)
VCOM_MEA: Q8.2 (S), R65.2, U14.39 (GPIO27_ADC1)
VCOM_MEA_EN: R66.2, U14.38 (GPIO26_ADC0)
VGH: C41.2, C44.2, C62.1, D2.1 (K), J3.3, R24.2
VGL: C33.1, C46.1, C63.1, D3.2 (A), D6.2 (A), J3.1, R19.1, R33.1, U9.2 (GND)
VNEG: C34.1, C47.1, C50.1, C54.2, D4.2 (A), D6.1 (K), J3.38, R21.1, R26.1, R34.1, R62.2, U10.2 (GND), U11.2 (V-)
VPOS: C40.2, C43.2, C48.2, D1.1 (K), J3.36, R22.2

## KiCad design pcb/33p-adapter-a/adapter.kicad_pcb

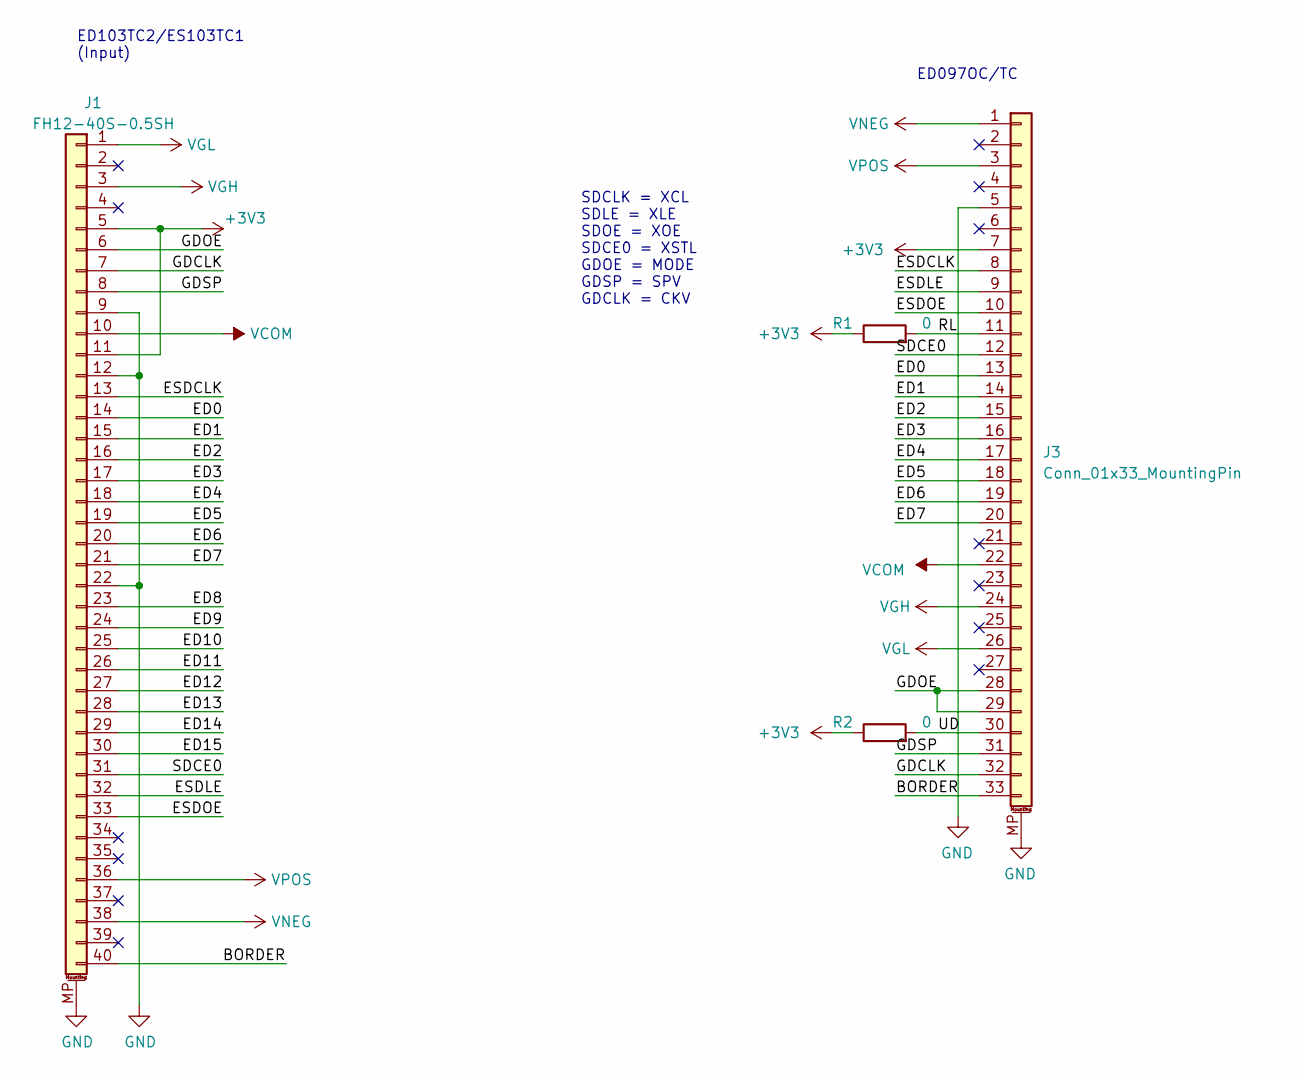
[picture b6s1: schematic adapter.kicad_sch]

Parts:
J1: FH12-40S-0.5SH; Hirose_FH12-40S-0.5SH_1x40-1MP_P0.50mm_Horizontal_Reversed
J3: Conn_01x33_MountingPin; Hirose_FH12-33S-0.5SH_1x33-1MP_P0.50mm_Horizontal
R1, R2: 0; R_0402_1005Metric

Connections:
+3V3: J1.5, J1.11, J3.7, R1.1, R2.1
/BORDER: J1.40, J3.33
/ED0: J1.14, J3.13
/ED1: J1.15, J3.14
/ED2: J1.16, J3.15
/ED3: J1.17, J3.16
/ED4: J1.18, J3.17
/ED5: J1.19, J3.18
/ED6: J1.20, J3.19
/ED7: J1.21, J3.20
/ED8: J1.23
/ED9: J1.24
/ED10: J1.25
/ED11: J1.26
/ED12: J1.27
/ED13: J1.28
/ED14: J1.29
/ED15: J1.30
/ESDCLK: J1.13, J3.8
/ESDLE: J1.32, J3.9
/ESDOE: J1.33, J3.10
/GDCLK: J1.7, J3.32
/GDOE: J1.6, J3.28, J3.29
/GDSP: J1.8, J3.31
/RL: J3.11, R1.2
/SDCE0: J1.31, J3.12
/UD: J3.30, R2.2
GND: J1.9, J1.12, J1.22, J1.MP (MountPin), J3.5, J3.MP (MountPin)
VCOM: J1.10, J3.22
VGH: J1.3, J3.24
VGL: J1.1, J3.26
VNEG: J1.38, J3.1
VPOS: J1.36, J3.3

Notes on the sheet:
ED103TC2/ES103TC1 (Input)
ED097OC/TC
SDCLK = XCL SDLE = XLE SDOE = XOE SDCE0 = XSTL GDOE = MODE GDSP = SPV GDCLK = CKV

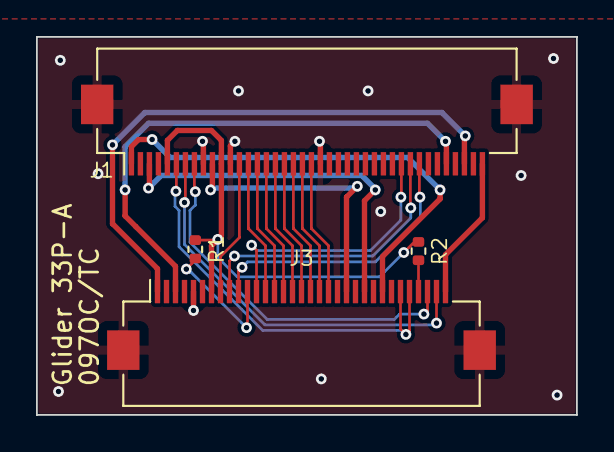
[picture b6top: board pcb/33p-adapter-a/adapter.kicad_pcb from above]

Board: 2 copper layers, 30.0 x 21.0 mm, 4 parts (0 on the bottom side), 25 nets.

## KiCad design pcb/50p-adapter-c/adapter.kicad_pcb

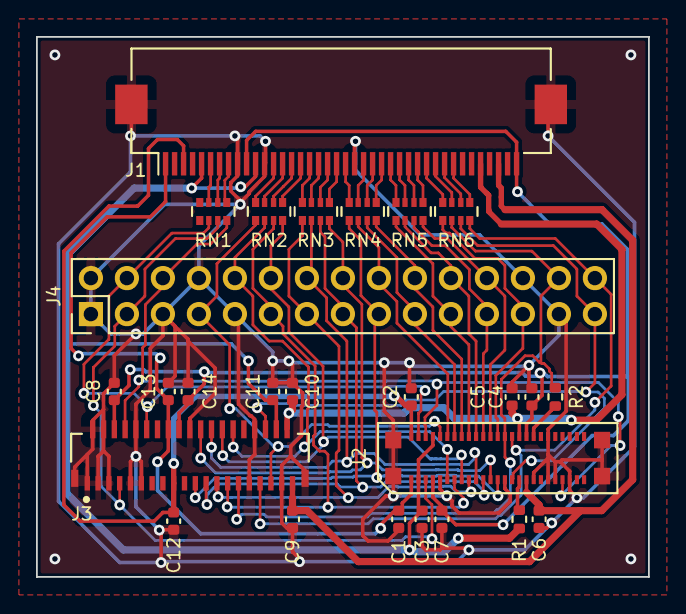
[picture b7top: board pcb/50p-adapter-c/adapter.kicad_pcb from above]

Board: 2 copper layers, 34.0 x 30.0 mm, 26 parts (0 on the bottom side), 55 nets.

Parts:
C1, C2, C3, C4, C5, C6, C7, C8, C9, C10, C11, C12, C13, C14: 220nF; C_0402_1005Metric
J1: FH12-40S-0.5SH; Hirose_FH12-40S-0.5SH_1x40-1MP_P0.50mm_Horizontal_Reversed
J2: AXE550127
J3: 10064555-392120HLF; FCI_10064555-392120HLF
J4: Conn_02x15_Odd_Even; PinHeader_2x15_P2.00mm_Vertical
R1: 10K; R_0402_1005Metric
R2: 0R; R_0402_1005Metric
RN1, RN2, RN3, RN4, RN5, RN6: 33; R_Array_Convex_4x0402

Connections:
+3V3: C3.1, C11.1, J1.5, J1.11, J2.3, J2.8, J3.4, R1.1
/ED0: J2.11, J3.12, J4.10, RN2.6 (R3.2)
/ED1: J2.13, J3.13, J4.11, RN2.7 (R2.2)
/ED2: J2.15, J3.14, J4.12, RN2.8 (R1.2)
/ED3: J2.17, J3.15, J4.13, RN3.5 (R4.2)
/ED4: J2.19, J3.16, J4.14, RN3.6 (R3.2)
/ED5: J2.21, J3.17, J4.15, RN3.7 (R2.2)
/ED6: J2.23, J3.18, J4.16, RN3.8 (R1.2)
/ED7: J2.25, J3.19, J4.17, RN4.5 (R4.2)
/ED8: J2.12, J4.18, RN4.6 (R3.2)
/ED9: J2.14, J4.19, RN4.7 (R2.2)
/ED10: J2.16, J4.20, RN4.8 (R1.2)
/ED11: J2.18, J4.21, RN5.5 (R4.2)
/ED12: J2.20, J4.22, RN5.6 (R3.2)
/ED13: J2.22, J4.23, RN5.7 (R2.2)
/ED14: J2.24, J4.24, RN5.8 (R1.2)
/ED15: J2.26, J4.25, RN6.5 (R4.2)
/ESDCLK: J2.10, J3.5, J4.7, RN2.5 (R4.2)
/ESDLE: J2.29, J3.6, J4.29, RN6.7 (R2.2)
/ESDOE: J2.30, J3.7, J4.30, RN6.8 (R1.2)
/GDCLK: J2.5, J3.33, J4.3, RN1.7 (R2.2)
/GDOE: J2.4, J3.28, J4.4, RN1.6 (R3.2)
/GDSP: J2.6, J2.43, J3.32, J4.6, RN1.8 (R1.2)
/SDCE0: J2.28, J3.11, J4.28, R2.1, RN6.6 (R3.2)
GND: C1.2, C2.2, C3.2, C4.2, C5.2, C6.2, C7.2, C8.2, C9.2, C10.2, C11.2, C12.2, C13.2, C14.2, J1.9, J1.12, J1.22, J1.MP (MountPin), J2.9, J2.27, J2.35, J2.39, J2.40, J2.41, J2.45, J2.MP (MountPin), J3.3, J3.8, J3.9, J3.20, J3.29, J3.30, J3.31, J3.35, J3.36, J3.37, J3.38, J3.39, J3.MP (MountPin), J4.1, J4.2, J4.5, J4.8, J4.9, J4.26, J4.27
unnamed: J1.6, RN1.3 (R3.1)
unnamed: J1.7, RN1.2 (R2.1)
unnamed: J1.8, RN1.1 (R1.1)
unnamed: J1.13, RN2.4 (R4.1)
unnamed: J1.14, RN2.3 (R3.1)
unnamed: J1.15, RN2.2 (R2.1)
unnamed: J1.16, RN2.1 (R1.1)
unnamed: J1.17, RN3.4 (R4.1)
unnamed: J1.18, RN3.3 (R3.1)
unnamed: J1.19, RN3.2 (R2.1)
unnamed: J1.20, RN3.1 (R1.1)
unnamed: J1.21, RN4.4 (R4.1)
unnamed: J1.23, RN4.3 (R3.1)
unnamed: J1.24, RN4.2 (R2.1)
unnamed: J1.25, RN4.1 (R1.1)
unnamed: J1.26, RN5.4 (R4.1)
unnamed: J1.27, RN5.3 (R3.1)
unnamed: J1.28, RN5.2 (R2.1)
unnamed: J1.29, RN5.1 (R1.1)
unnamed: J1.30, RN6.4 (R4.1)
unnamed: J1.31, RN6.3 (R3.1)
unnamed: J1.32, RN6.2 (R2.1)
unnamed: J1.33, RN6.1 (R1.1)
unnamed: J2.31, R1.2
unnamed: J2.36, R2.2
VCOM: C4.1, C7.1, C8.1, C14.1, J1.10, J1.40, J2.7, J2.34, J3.22, J3.34
VGH: C2.1, C12.1, J1.3, J2.2, J3.23
VGL: C1.1, C13.1, J1.1, J2.1, J3.24
VNEG: C6.1, C9.1, J1.38, J2.33, J3.1
VPOS: C5.1, C10.1, J1.36, J2.32, J3.2

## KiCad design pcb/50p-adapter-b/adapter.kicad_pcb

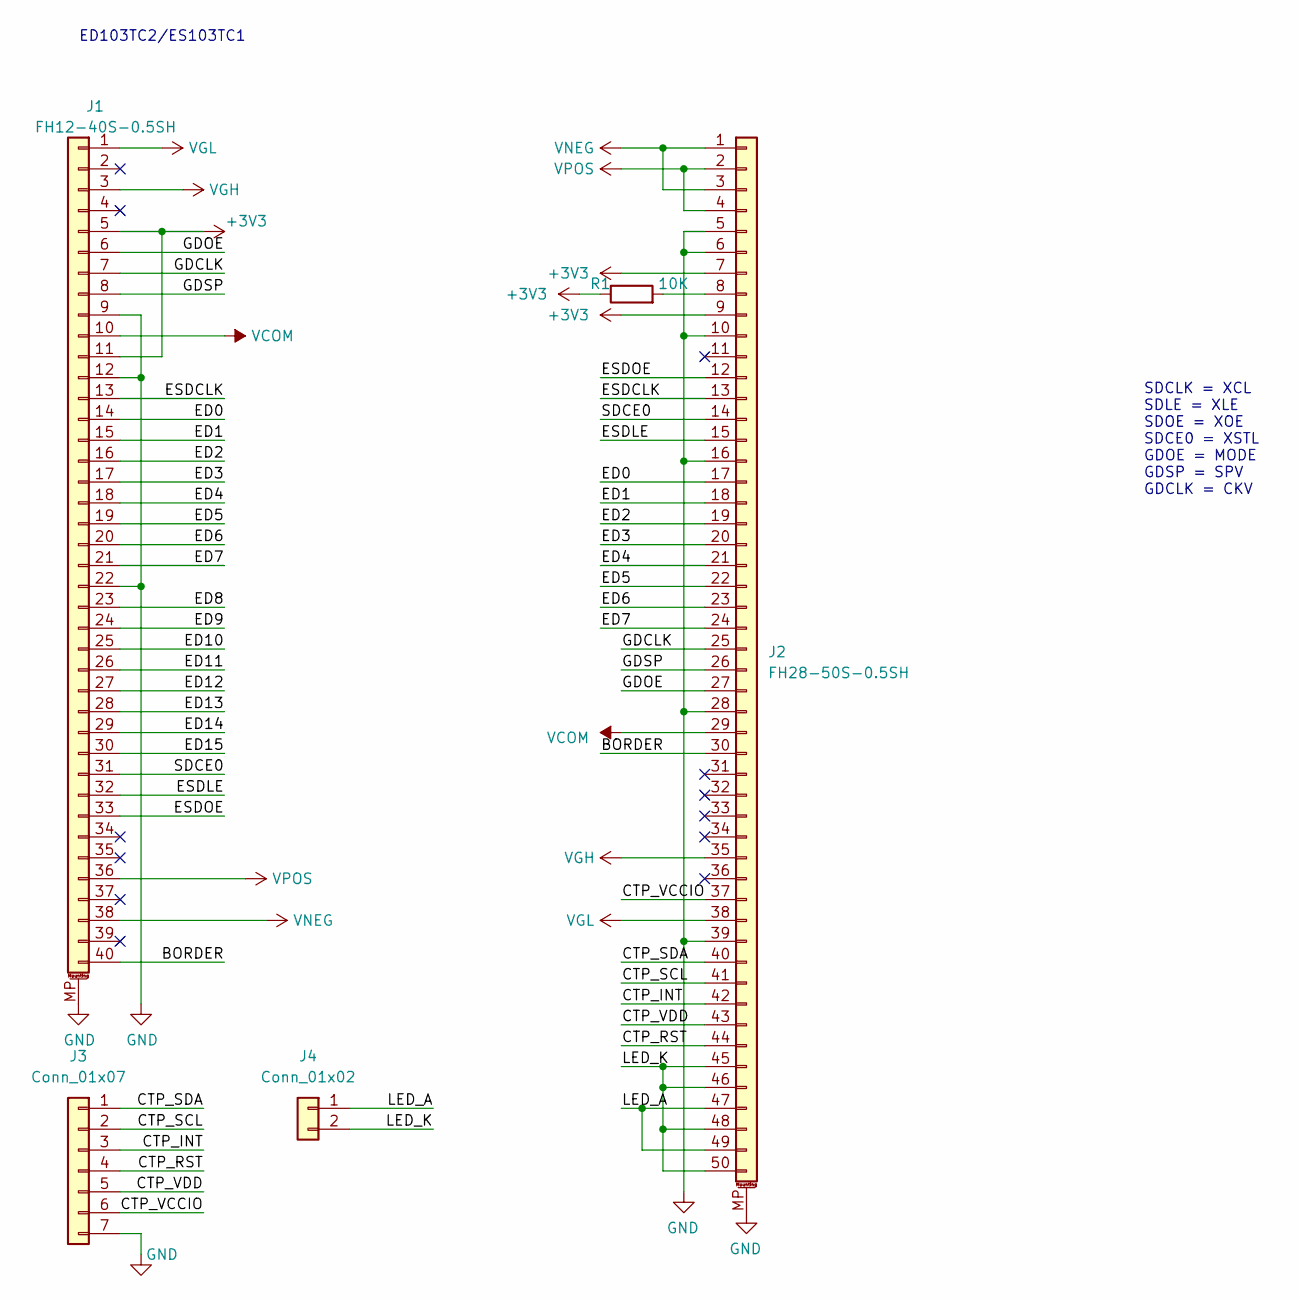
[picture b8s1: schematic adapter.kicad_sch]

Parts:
J1: FH12-40S-0.5SH; Hirose_FH12-40S-0.5SH_1x40-1MP_P0.50mm_Horizontal_Reversed
J2: FH28-50S-0.5SH; BM20B-0.8-50
J3: Conn_01x07; PinHeader_1x07_P2.54mm_Vertical
J4: Conn_01x02; PinHeader_1x02_P2.54mm_Vertical
R1: 10K; R_0402_1005Metric

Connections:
+3V3: J1.5, J1.11, J2.7, J2.9, R1.1
/BORDER: J1.40, J2.30
/CTP_INT: J2.42, J3.3
/CTP_RST: J2.44, J3.4
/CTP_SCL: J2.41, J3.2
/CTP_SDA: J2.40, J3.1
/CTP_VCCIO: J2.37, J3.6
/CTP_VDD: J2.43, J3.5
/ED0: J1.14, J2.17
/ED1: J1.15, J2.18
/ED2: J1.16, J2.19
/ED3: J1.17, J2.20
/ED4: J1.18, J2.21
/ED5: J1.19, J2.22
/ED6: J1.20, J2.23
/ED7: J1.21, J2.24
/ED8: J1.23
/ED9: J1.24
/ED10: J1.25
/ED11: J1.26
/ED12: J1.27
/ED13: J1.28
/ED14: J1.29
/ED15: J1.30
/ESDCLK: J1.13, J2.13
/ESDLE: J1.32, J2.15
/ESDOE: J1.33, J2.12
/GDCLK: J1.7, J2.25
/GDOE: J1.6, J2.27
/GDSP: J1.8, J2.26
/LED_A: J2.47, J2.49, J4.1
/LED_K: J2.45, J2.46, J2.48, J2.50, J4.2
/SDCE0: J1.31, J2.14
GND: J1.9, J1.12, J1.22, J1.MP (MountPin), J2.5, J2.6, J2.10, J2.16, J2.28, J2.39, J2.MP (MountPin), J3.7
unnamed: J2.8, R1.2
VCOM: J1.10, J2.29
VGH: J1.3, J2.35
VGL: J1.1, J2.38
VNEG: J1.38, J2.1, J2.3
VPOS: J1.36, J2.2, J2.4

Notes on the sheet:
SDCLK = XCL SDLE = XLE SDOE = XOE SDCE0 = XSTL GDOE = MODE GDSP = SPV GDCLK = CKV
ED103TC2/ES103TC1

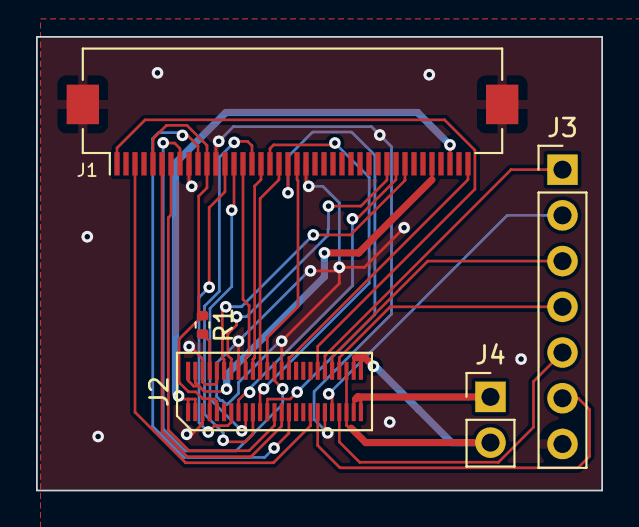
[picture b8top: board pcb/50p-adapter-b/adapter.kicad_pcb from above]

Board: 2 copper layers, 31.4 x 25.2 mm, 5 parts (0 on the bottom side), 32 nets.
